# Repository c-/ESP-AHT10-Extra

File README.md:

# ESP-AHT10-Extra

Minimalist/compact ESP-8266 environmental sensor/programmer.

This is a Kicad design which uses a PCB USB connector and integrates a
ESP-12 (or 07), CH330N USB controller, a small voltage regulator
(HT7233), an AHT-10 temperature/humidity sensor, and a VEML-7700
ambient light sensor. Flash and reset buttons are also included.

My prototype was done on a PCB mill (0.3mm 30 degree V-bit), so things
like trace sizes and clearances reflect that. 0805 passives are used since
that's as small as I can go and still be able to route a trace between
the pads.

![Milled
Back](https://github.com/c-/ESP-AHT10-Extra/blob/master/Images/bare_1.6.jpg)

If you don't want to roll your own PCB's, [Oshpark does a nice job on these
at a great price](https://oshpark.com/shared_projects/kst87h07). The PCB is
approx 39mm x 21mm.

# Assembly

This PCB is designed for reflow soldering of the SMD components (I use
hot air). I'm sure someone *can* hand solder it, but it wouldn't be me.

Either or both sensors can be left off entirely, as the application
dictates.

R3 should be left out if the ESP modules being used have an
internal pullup between RST and 3V3 (which most newer ones seem to
have). Otherwise, you end up with a combined pullup resistance near 5k,
and GPIO16 though a 1k resistor seems to struggle to pulse that long
enough to perform a proper wake. With the modules I've tested (ESP-12E,
ESP-12F, ESP-07) there's been no issues with deep sleep wake and R3
unpopulated.

I usually mount my ESP modules on 2mm pin headers. It's not really
necessary unless you screw up designs as often as I do. However, doing so
technically makes all the USB stuff optional for some boards since I can
just remove the module for programming. On the other hand, I'm keeping the
USB stuff as I'm finding these boards are an extremely convenient programmers
for my pluggable modules.

The standard 1.6mm PCB is too thin to solidly fit most USB ports. I use
a thin (0.5mm) 3D printed shim on the front to bring the thickness up.
I've milled my latest from 2.17mm thick FR4 and it fits a port perfectly.

# Usage

The temperature sensor is mounted to the backside of the board from the
ESP-8266. Practically speaking, this means that unless you want to monitor
the temperature of the MCU, you need the device to spend as much time in
deep sleep as needed to bring the temperature down to ambient. When waking
up, it's best to take the temperature reading ASAP during startup,
prior to doing something like a DHCP connect, during which the
ESP starts to ramp up the temperatures. Testing shows that this sort of
delay can spike the temperature reading by 0.5C or more. I expect that
a combination of deep sleep and ESP-NOW would be ideal.

I still not sure what I'm going to use the ambient light sensor,
but it fits the design nicely. Unfortunately, orientation matters and not
all USB jacks are going to cooperate with that.

A minimal example sketch is included. It requires an AHT10 library (I
rolled my own, at https://github.com/c-/SnoutnetAHT10/, but others exists,
YYMV, etc) and the VEML-7700 library at
https://github.com/tedyapo/arduino-VEML7700.

v1.5 of the board used the LTR-303 ambient light sensor. I haven't been a
fan of the stability of that device. The VEML-7700 Just Works.

# Design Notes

The CH330N is running off the 5V rail, which *technically* means it's
driving the ESP UART at (allowing for a 0.3v drop from D1) approx 4.2V,
which is clearly above the 3.6V rated max for the ESP. In practice, the
ESP-8266 is quite 5V tolerant on GPIO's, and the CH330N only drives at
something like 4mA, so this probably isn't worth worrying about.

I've found that 10K pullups on the I2C sensors works in most cases, but
4.7K might be better. Still testing that.

The HT7233 is a perfectly fine regulator, but most similar
SOT-23-3 regulators rated for at least 250mA should work. Just check the
pinout.

No auto-reset/program circuit is included; you'll have to use buttons like
some kind of caveman.

# Bill of Materials

Most parts are from LCSC. Some of these choices aren't ideal, but I had
them on hand and they work.  A design based around one of the more common
DFN-6 sensors like the Si70xx series might happen down the road. I'm also
seriously considering a design based on a SOT-23-6 temperature sensor like
the LM73, as humidity isn't quite so critical for most of my applications.
Note that the photos show 1% resistors; that precision is not *necessary*,
it's just what I usually buy.

* ESP-12 (I *usually* mount mine on 2mm pin headers)
* [Aosong AHT-10 Temperature/Humidity Sensor](https://lcsc.com/product-detail/Temperature-Humidity-Sensors_Aosong-Guangzhou-Elec-AHT10_C368909.html)
* [VEML7700 Ambient Light Sensor](https://www.digikey.ca/product-detail/en/vishay-semiconductor-opto-division/VEML7700-TT/751-VEML7700-TTCT-ND/10817048)
* [CH330N USB Controller](https://lcsc.com/product-detail/USB-ICs_Jiangsu-Qin-Heng-CH330N_C108996.html)
* [Holtek HT-7233 SOT-23-3](https://lcsc.com/product-detail/Low-Dropout-Regulators-LDO_Holtek-Semicon-HT7233_C47970.html)
* [STMicroelectronics USBLC6-2SC6 SOT-23-6](https://lcsc.com/product-detail/Diodes-ESD_STMicroelectronics_USBLC6-2SC6_USBLC6-2SC6_C7519.html)
* 100nF 0805 capacitors
* 10uF 0805 capacitors
* 10k 0805 resistors
* 1k 0805 resistor
* 470R 0805 resistor
* [B5817W SOD-123F Schottky barrier diode](https://lcsc.com/product-detail/Schottky-Barrier-Diodes-SBD_Shikues-B5817WL_C122853.html)
* [350mA (hold) 0805 fuse](https://lcsc.com/product-detail/PTC-Resettable-Fuses_BOURNS-MF-PSMF035X-2_C116172.html)
* [SPST Tactile Switches](https://lcsc.com/product-detail/Tactile-Switches_HYP-Hongyuan-Precision-1TS002A-2300-5000_C318817.html)

Strictly speaking, most of the USB protection components aren't
*necessary* for a simple sensor device, but I had the parts and the
space...

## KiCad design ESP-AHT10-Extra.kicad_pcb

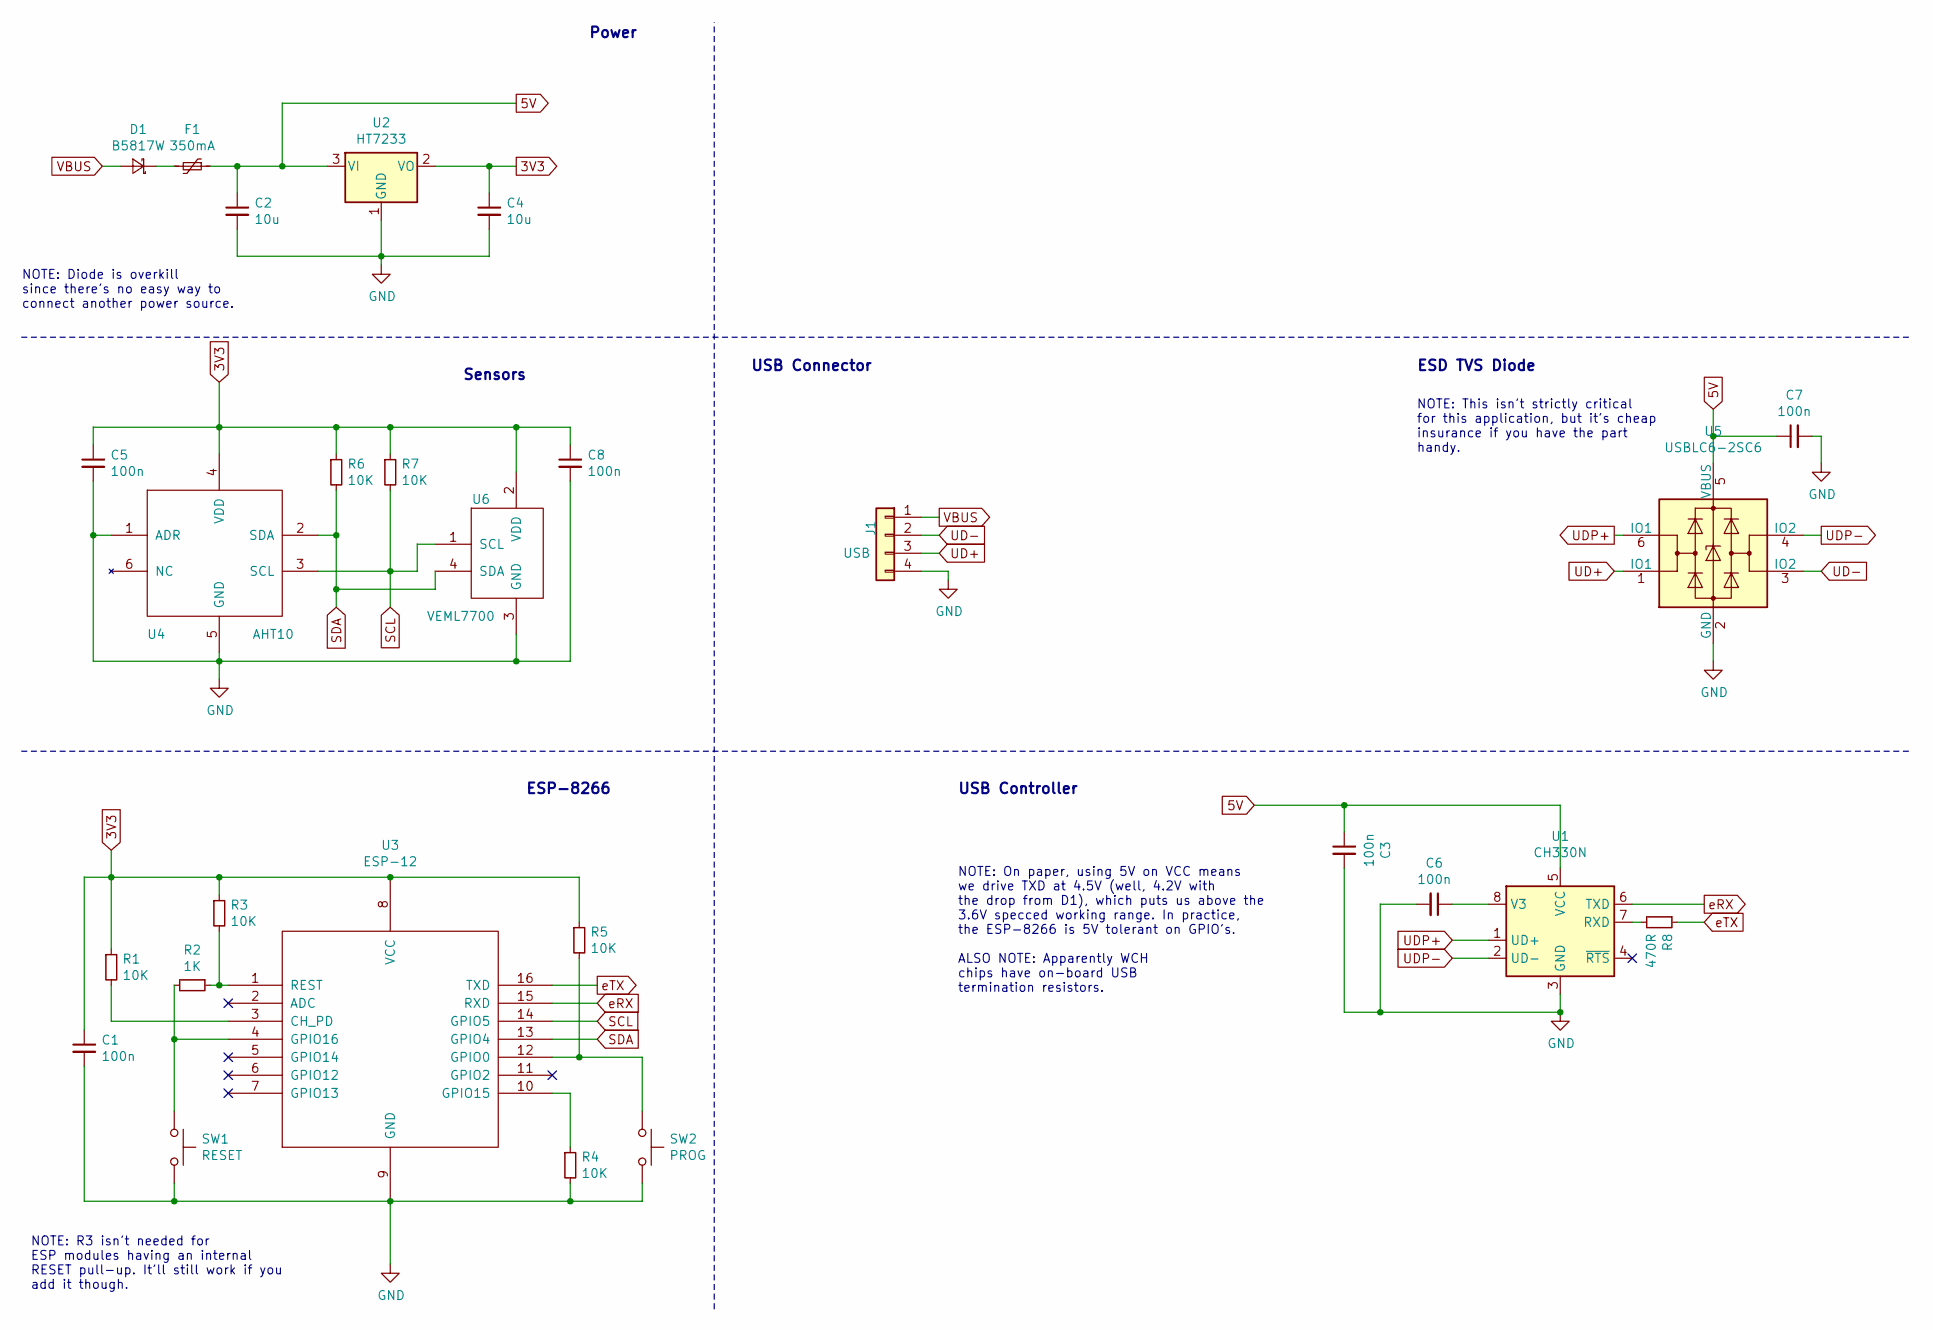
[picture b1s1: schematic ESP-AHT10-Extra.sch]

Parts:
C1, C3, C5, C6, C7, C8: 100n; C_0805_2012Metric
C2, C4: 10u; C_0805_2012Metric
D1: B5817W; D_SOD-123F
F1: 350mA; Fuse_0805_2012Metric
J1: USB; usb-PCB
R1, R3, R4, R5, R6, R7: 10K; R_0805_2012Metric
R2: 1K; R_0805_2012Metric
R8: 470R; R_0805_2012Metric
SW1: RESET; Tact Switch 6mmx3.5mm C318817
SW2: PROG; Tact Switch 6mmx3.5mm C318817
U1: CH330N; SOIC-8_3.9x4.9mm_P1.27mm
U2: HT7233; SOT-23
U3: ESP-12; ESP-12Emin
U4: AHT10; AHT10-HandSolder
U5: USBLC6-2SC6; SOT-23-6
U6: VEML7700

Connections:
3V3: C1.1, C4.1, C5.1, C8.1, R1.1, R3.1, R5.1, R6.1, R7.1, U2.2 (VO), U3.8 (VCC), U4.4 (VDD), U6.2 (VDD)
5V: C2.1, C3.1, C7.1, F1.1, U1.5 (VCC), U2.3 (VI), U5.5 (VBUS)
GND: C1.2, C2.2, C3.2, C4.2, C5.2, C6.2, C7.2, C8.2, J1.4, R4.2, SW1.2, SW2.2, U1.3 (GND), U2.1 (GND), U3.9 (GND), U4.1 (ADR), U4.5 (GND), U5.2 (GND), U6.3 (GND)
unnamed: C6.1, U1.8 (V3)
unnamed: D1.1 (K), F1.2
unnamed: R1.2, U3.3 (CH_PD)
unnamed: R2.1, R3.2, U3.1 (REST)
unnamed: R2.2, SW1.1, U3.4 (GPIO16)
unnamed: R4.1, U3.10 (GPIO15)
unnamed: R5.2, SW2.1, U3.12 (GPIO0)
unnamed: R8.2, U1.7 (RXD)
SCL: R7.2, U3.14 (GPIO5), U4.3 (SCL), U6.1 (SCL)
SDA: R6.2, U3.13 (GPIO4), U4.2 (SDA), U6.4 (SDA)
UD+: J1.3, U5.1 (IO1)
UD-: J1.2, U5.3 (IO2)
UDP+: U1.1 (UD+), U5.6 (IO1)
UDP-: U1.2 (UD-), U5.4 (IO2)
VBUS: D1.2 (A), J1.1
eRX: U1.6 (TXD), U3.15 (RXD)
eTX: R8.1, U3.16 (TXD)

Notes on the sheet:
NOTE: On paper, using 5V on VCC means we drive TXD at 4.5V (well, 4.2V with the drop from D1), which puts us above the 3.6V specced working range. In practice, the ESP-8266 is 5V tolerant on GPIO's. ALSO NOTE: Apparently WCH chips have on-board USB termination resistors.
USB Connector
Power
ESD TVS Diode
USB Controller
Sensors
ESP-8266
NOTE: This isn't strictly critical for this application, but it's cheap insurance if you have the part handy.
NOTE: Diode is overkill since there's no easy way to connect another power source.
NOTE: R3 isn't needed for ESP modules having an internal RESET pull-up. It'll still work if you add it though.

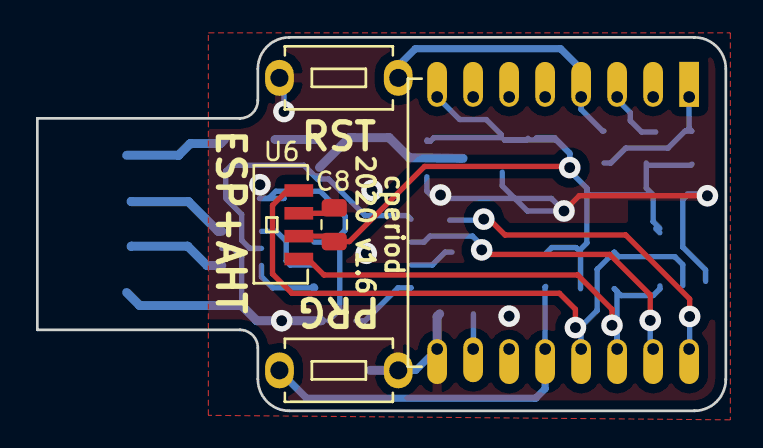
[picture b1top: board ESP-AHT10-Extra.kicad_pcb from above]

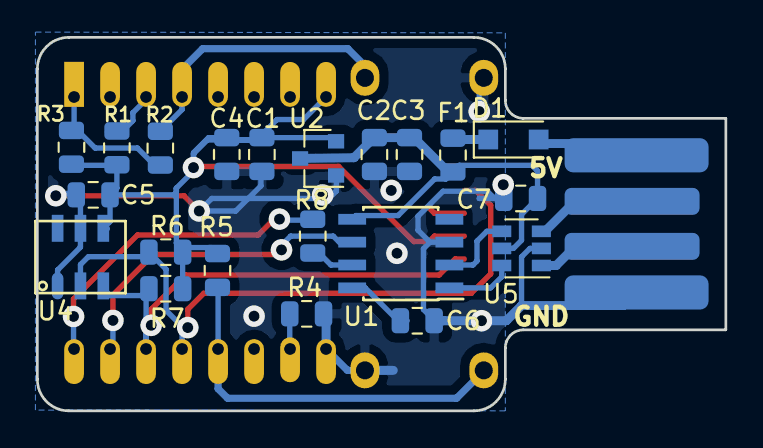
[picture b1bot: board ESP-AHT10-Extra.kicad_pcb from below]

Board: 2 copper layers, 38.2 x 20.8 mm, 27 parts (22 on the bottom side), 20 nets.

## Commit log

2019-11-04 3mm shorter
2019-11-04 more tweaking
2019-11-04 add USB ESD protection
2019-11-04 add a fuse. Don't need to fry another sensor...
2019-11-10 round all the corners
2019-11-10 drop vias to 0.6mm
2019-11-10 bump rev
2019-11-11 fix V3 connections to CH330N, bump the bulk caps to 10uF, rev number
2019-11-11 switch CH300N to 5V, add 330R resistors to TX/RD, tweak GPIO0 connection, adjust ground connections
2019-11-11 more direct 5V routing
2019-11-11 more fine tuning, layout cleanup, stability fixes
2019-11-11 enlarge the keepout around the temp sensor
2019-11-11 fix filter cap on ESD diode
2019-11-13 alignment tweaks
2019-11-14 tidy up schematic, add some notes, etc.
2019-11-14 add some images
2019-11-14 add some library files
2019-11-14 plot the rest of the gerbers
2019-11-14 Add a PDF version of the schematic
2019-11-14 silly typo
2019-11-16 really no excuse not to connect RTS to RESET
2019-11-16 fix R8's value
2019-11-16 leave a bit more meat on the ground pours
2019-11-16 try adding a WLED.
2019-11-17 place WLED, tidy up after some footprint changes
2019-11-19 a comment on using the device
2019-11-19 drop the nightlight concept; it's not going to work with the power dissipation of a WLED. Clean things up for double-sided milling a bit more.
2019-11-20 minor silk tweaks
2019-11-22 some notes on the CH330N running on 5V.
2019-11-23 more notes on CH330N and 5V.
2019-12-09 Connecting the CH330N to RESET is a bad idea when it's running on bus voltage.
2019-12-09 remove the RESET label
2019-12-09 update notes
2019-12-27 drop that extra 10uF cap. Aside from no longer being needed, this was probably keeping us beyond the USB spec.
2020-01-07 photo of v1.3 PCB
2020-01-09 link to oshpark project
2020-01-10 cleanup some ground plane concerns swap to a SOT-23-3 footprint regulator bump rev to 1.5
2020-01-11 Add a LTR-303 ambient light sensor
2020-02-09 more work on getting the light sensor sorted
2020-02-09 add a very lean example for testing.
2020-02-10 oops, fix that inverted logic.
2020-02-10 fix it better
2020-02-10 more comments
2020-02-10 okay, that sensor is way more picky than I like
2020-02-10 doc update
2020-02-10 add some new images and update the docs
2020-02-10 schematic update
2020-03-10 switch the ALS to the VEML7700. Seems a lot less flaky, but a *lot* bigger.
2020-03-17 a few trace tweaks
2020-03-17 update the sample sketch for the VEML7700
2020-03-17 update the documentation and whatnot.
